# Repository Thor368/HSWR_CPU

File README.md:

# HSWR_CPU
This is the CPU board of the HochSchulWechselRichter V1 (HSWR1_CPU)

Differences to VESC:
- no FAULT pin
- no DC_cal pin
- EN_GATE inverted

This project is depricated and was replaced by the HSWR2:
https://github.com/Thor368/HSWR_V2

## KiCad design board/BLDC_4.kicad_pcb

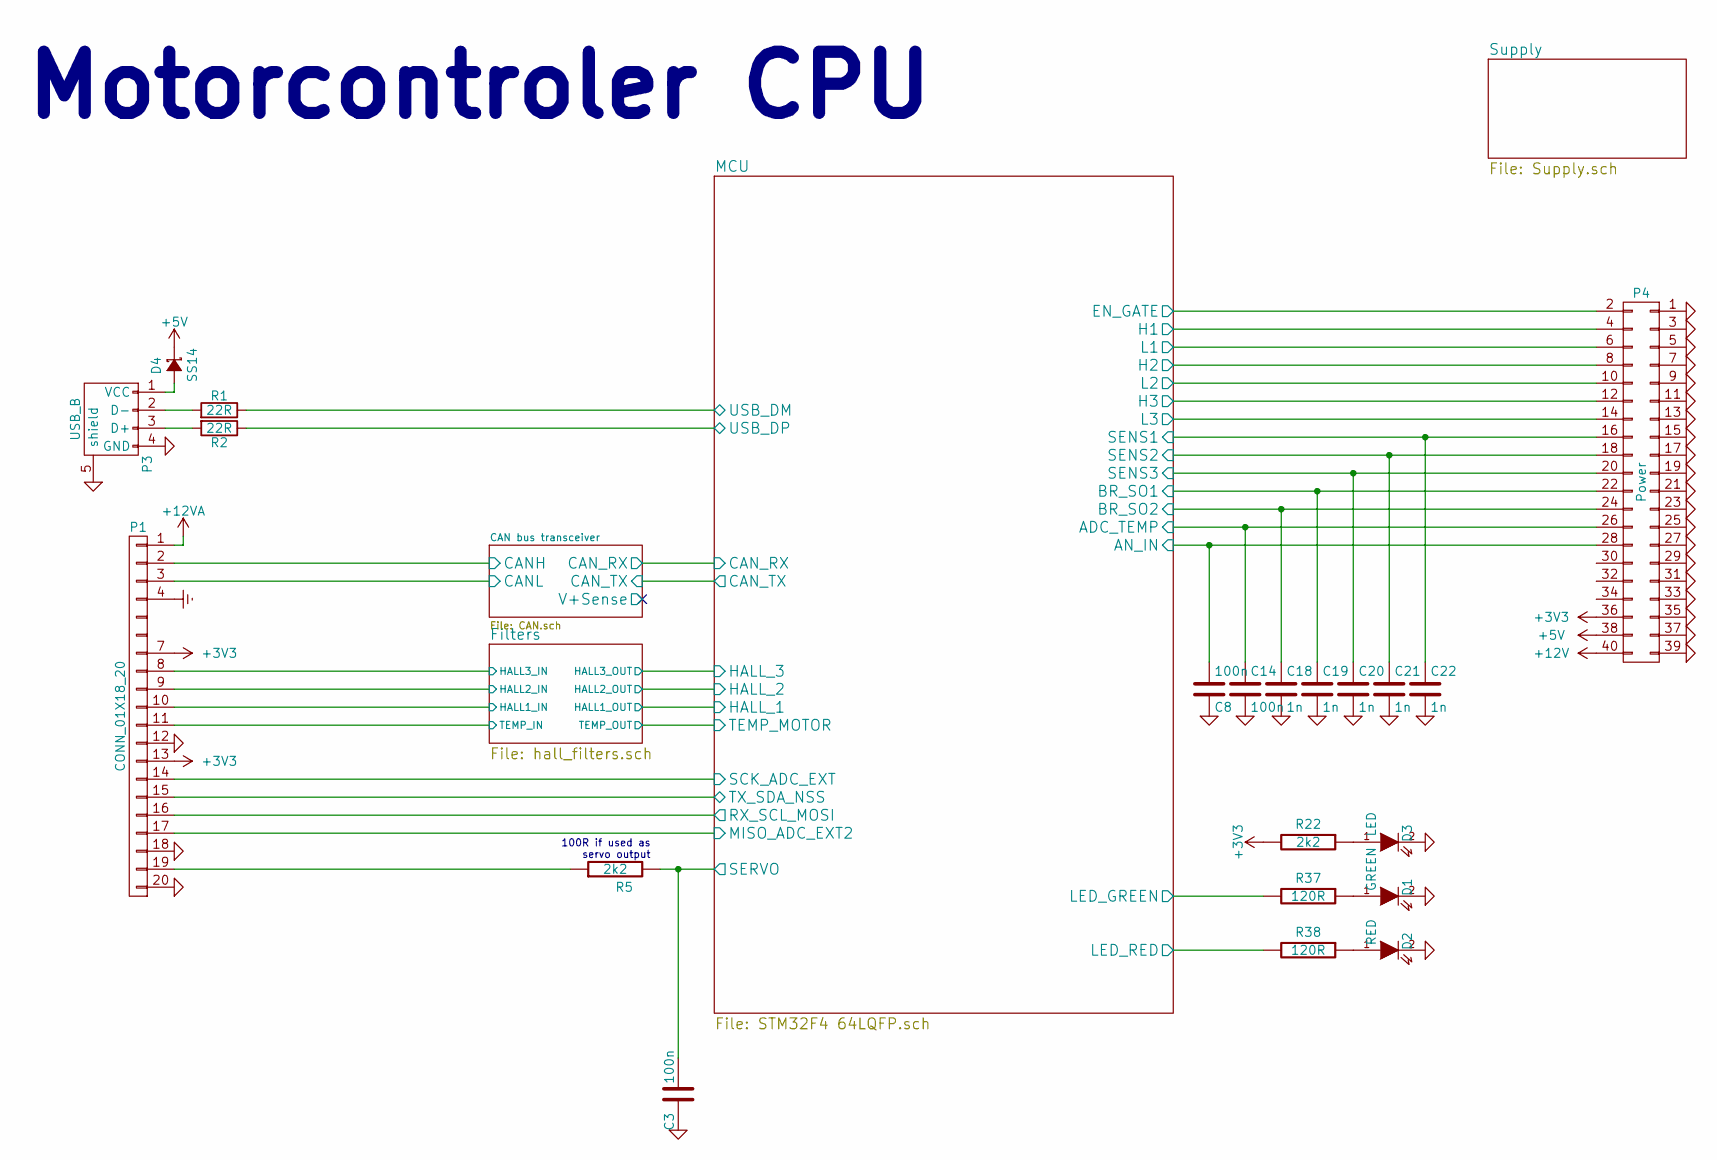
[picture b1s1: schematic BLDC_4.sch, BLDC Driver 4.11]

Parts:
C3, C8, C14: 100n; C_0805
C18, C19, C20, C21, C22: 1n; C_0805
D1: GREEN; LED_0805
D2: RED; LED_0805
D3: LED; LED_0805
D4: SS14; SMA_Standard
P1: CONN_01X18_20; XG4A_20_wo_56
P3: USB_B; USBB_vert
P4: Power; XG4A_40
R1, R2: 22R; R_0805
R5, R22: 2k2; R_0805
R37, R38: 120R; R_0805

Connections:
+3V3: P1.7, P1.13, P4.36, R22.2; also elsewhere on the board
+5V: D4.1 (K), P4.38; also elsewhere on the board
+12V: P4.40; also elsewhere on the board
+12VA: P1.1; also elsewhere on the board
/CAN bus transceiver/CANH: P1.2; also elsewhere on the board
/CAN bus transceiver/CANL: P1.3; also elsewhere on the board
/Filters/HALL1_IN: P1.10; also elsewhere on the board
/Filters/HALL2_IN: P1.9; also elsewhere on the board
/Filters/HALL3_IN: P1.8; also elsewhere on the board
/Filters/TEMP_IN: P1.11; also elsewhere on the board
/MCU/ADC_TEMP: C14.1, P4.26; also elsewhere on the board
/MCU/AN_IN: C8.2, P4.28; also elsewhere on the board
/MCU/BR_SO1: C19.1, P4.22; also elsewhere on the board
/MCU/BR_SO2: C18.1, P4.24; also elsewhere on the board
/MCU/EN_GATE: P4.2; also elsewhere on the board
/MCU/H1: P4.4; also elsewhere on the board
/MCU/H2: P4.8; also elsewhere on the board
/MCU/H3: P4.12; also elsewhere on the board
/MCU/L1: P4.6; also elsewhere on the board
/MCU/L2: P4.10; also elsewhere on the board
/MCU/L3: P4.14; also elsewhere on the board
/MCU/LED_GREEN: R37.2; also elsewhere on the board
/MCU/LED_RED: R38.2; also elsewhere on the board
/MCU/MISO_ADC_EXT2: P1.17; also elsewhere on the board
/MCU/RX_SCL_MOSI: P1.16; also elsewhere on the board
/MCU/SCK_ADC_EXT: P1.14; also elsewhere on the board
/MCU/SENS1: C22.1, P4.16; also elsewhere on the board
/MCU/SENS2: C21.1, P4.18; also elsewhere on the board
/MCU/SENS3: C20.1, P4.20; also elsewhere on the board
/MCU/SERVO: C3.2, R5.2; also elsewhere on the board
/MCU/TX_SDA_NSS: P1.15; also elsewhere on the board
/MCU/USB_DM: R1.1; also elsewhere on the board
/MCU/USB_DP: R2.1; also elsewhere on the board
Earth: P1.4; also elsewhere on the board
GND: C3.1, C8.1, C14.2, C18.2, C19.2, C20.2, C21.2, C22.2, D1.2 (K), D2.2 (K), D3.2 (K), P1.12, P1.18, P1.20, P3.4 (GND), P3.5 (shield), P4.1, P4.3, P4.5, P4.7, P4.9, P4.11, P4.13, P4.15, P4.17, P4.19, P4.21, P4.23, P4.25, P4.27, P4.29, P4.31, P4.33, P4.35, P4.37, P4.39; also elsewhere on the board
unnamed: D1.1 (A), R37.1
unnamed: D2.1 (A), R38.1
unnamed: D3.1 (A), R22.1
unnamed: D4.2 (A), P3.1 (VCC)
unnamed: P1.19, R5.1
unnamed: P3.2 (D-), R1.2
unnamed: P3.3 (D+), R2.2

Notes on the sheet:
100R if used as servo output
Motorcontroler CPU

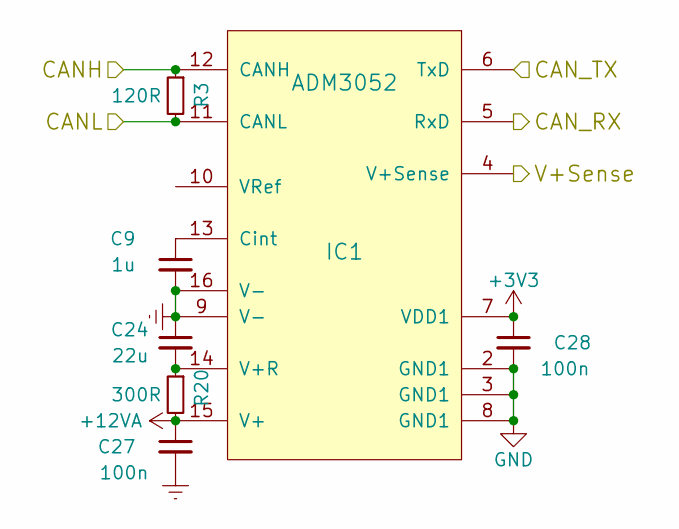
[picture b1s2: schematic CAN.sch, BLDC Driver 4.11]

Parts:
C9: 1u; C_0805
C24: 22u; C_0805
C27, C28: 100n; C_0805
IC1: ADM3052; SOIC-16_7.5x10.3mm_Pitch1.27mm
R3: 120R; R_0805
R20: 300R; R_1206

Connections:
+3V3: C28.1, IC1.7 (VDD1); also elsewhere on the board
+12VA: C27.1, IC1.15 (V+), R20.2; also elsewhere on the board
/CAN bus transceiver/CANH: IC1.12 (CANH), R3.1; also elsewhere on the board
/CAN bus transceiver/CANL: IC1.11 (CANL), R3.2; also elsewhere on the board
/CAN bus transceiver/CAN_RX: IC1.5 (RxD); also elsewhere on the board
/CAN bus transceiver/CAN_TX: IC1.6 (TxD); also elsewhere on the board
Earth: C9.2, C24.1, C27.2, IC1.9 (V-), IC1.16 (V-); also elsewhere on the board
GND: C28.2, IC1.2 (GND1), IC1.3 (GND1), IC1.8 (GND1); also elsewhere on the board
unnamed: C9.1, IC1.13 (Cint)
unnamed: C24.2, IC1.14 (V+R), R20.1

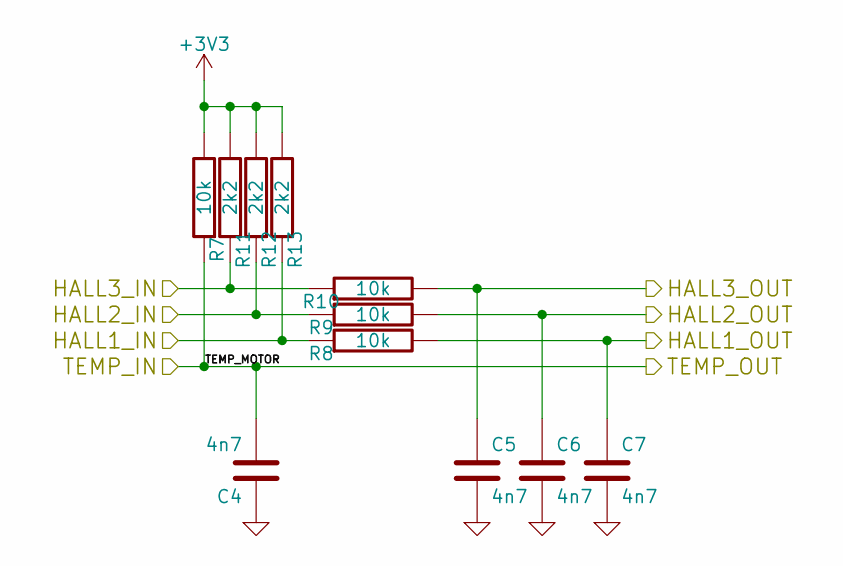
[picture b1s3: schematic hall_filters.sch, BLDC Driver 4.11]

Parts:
C4, C5, C6, C7: 4n7; C_0805
R7, R8, R9, R10: 10k; R_0805
R11, R12, R13: 2k2; R_0805

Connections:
+3V3: R7.2, R11.2, R12.2, R13.2; also elsewhere on the board
/Filters/HALL1_IN: R8.1, R13.1; also elsewhere on the board
/Filters/HALL1_OUT: C7.1, R8.2; also elsewhere on the board
/Filters/HALL2_IN: R9.1, R12.1; also elsewhere on the board
/Filters/HALL2_OUT: C6.1, R9.2; also elsewhere on the board
/Filters/HALL3_IN: R10.1, R11.1; also elsewhere on the board
/Filters/HALL3_OUT: C5.1, R10.2; also elsewhere on the board
/Filters/TEMP_IN: C4.2, R7.1; also elsewhere on the board
GND: C4.1, C5.2, C6.2, C7.2; also elsewhere on the board

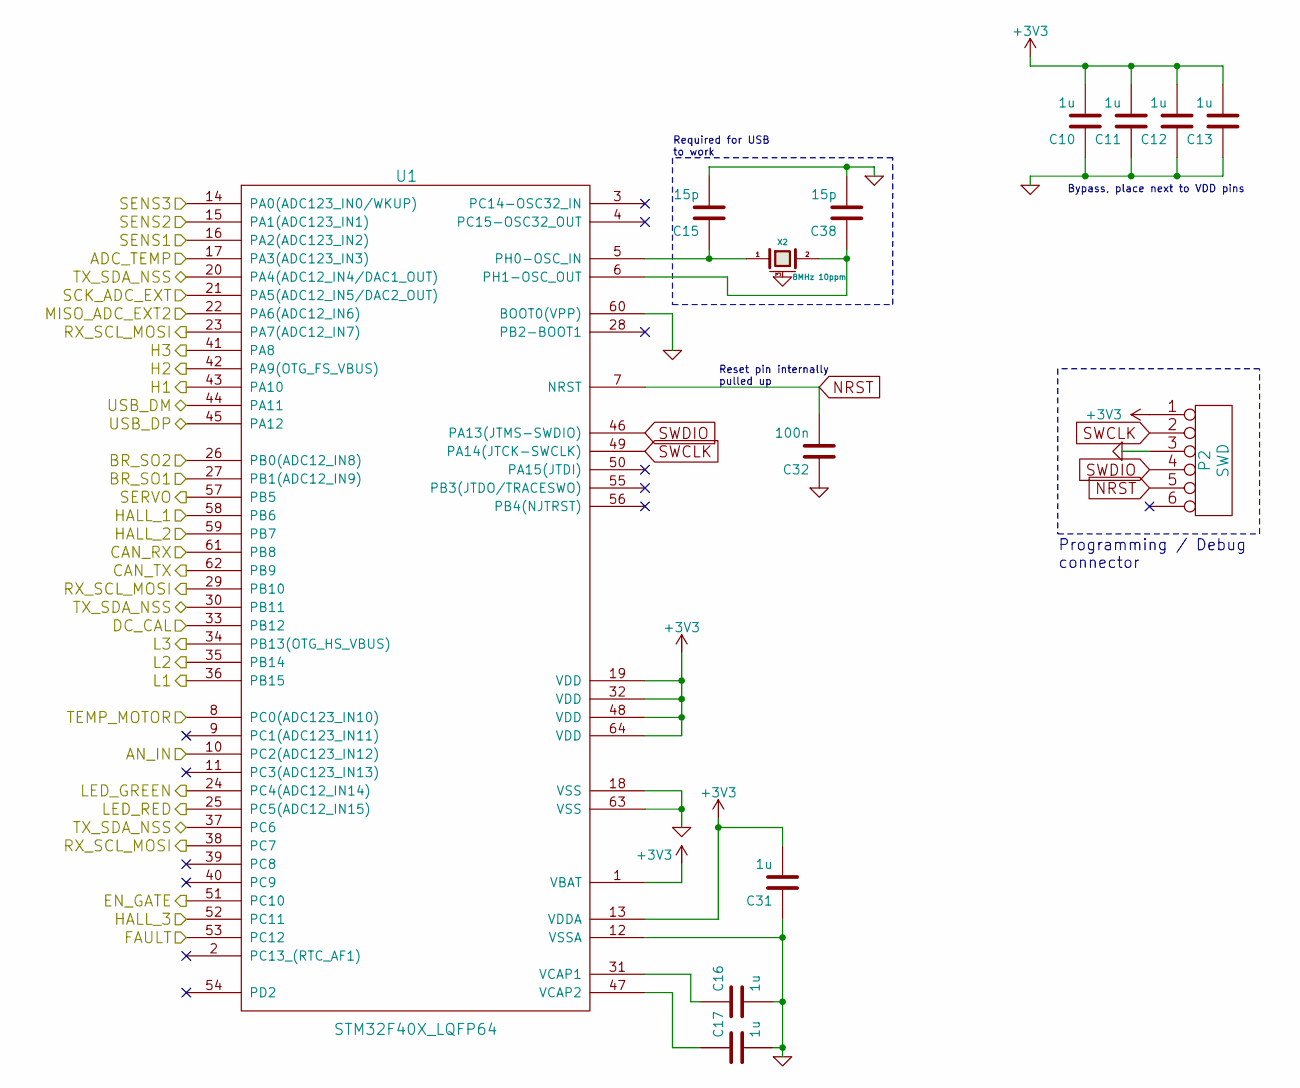
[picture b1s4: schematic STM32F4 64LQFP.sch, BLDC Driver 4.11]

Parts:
C10, C11, C12, C13, C16, C17, C31: 1u; C_0805
C15, C38: 15p; C_0805
C32: 100n; C_0805
P2: SWD; Pin_Header_Straight_2x03
U1: STM32F40X_LQFP64; LQFP-64_10x10mm_Pitch0.5mm
X2: 8MHz 10ppm; Crystal_HC49-U_Vertical; mfg# ABM3B-8.0-10-1UT

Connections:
+3V3: C10.2, C11.2, C12.2, C13.2, C31.2, P2.1, U1.1 (VBAT), U1.13 (VDDA), U1.19 (VDD), U1.32 (VDD), U1.48 (VDD), U1.64 (VDD); also elsewhere on the board
/CAN bus transceiver/CAN_RX: U1.61 (PB8); also elsewhere on the board
/CAN bus transceiver/CAN_TX: U1.62 (PB9); also elsewhere on the board
/Filters/HALL1_OUT: U1.58 (PB6); also elsewhere on the board
/Filters/HALL2_OUT: U1.59 (PB7); also elsewhere on the board
/Filters/HALL3_OUT: U1.52 (PC11); also elsewhere on the board
/Filters/TEMP_IN: U1.8 (PC0(ADC123_IN10)); also elsewhere on the board
/MCU/ADC_TEMP: U1.17 (PA3(ADC123_IN3)); also elsewhere on the board
/MCU/AN_IN: U1.10 (PC2(ADC123_IN12)); also elsewhere on the board
/MCU/BR_SO1: U1.27 (PB1(ADC12_IN9)); also elsewhere on the board
/MCU/BR_SO2: U1.26 (PB0(ADC12_IN8)); also elsewhere on the board
/MCU/EN_GATE: U1.51 (PC10); also elsewhere on the board
/MCU/H1: U1.43 (PA10); also elsewhere on the board
/MCU/H2: U1.42 (PA9(OTG_FS_VBUS)); also elsewhere on the board
/MCU/H3: U1.41 (PA8); also elsewhere on the board
/MCU/L1: U1.36 (PB15); also elsewhere on the board
/MCU/L2: U1.35 (PB14); also elsewhere on the board
/MCU/L3: U1.34 (PB13(OTG_HS_VBUS)); also elsewhere on the board
/MCU/LED_GREEN: U1.24 (PC4(ADC12_IN14)); also elsewhere on the board
/MCU/LED_RED: U1.25 (PC5(ADC12_IN15)); also elsewhere on the board
/MCU/MISO_ADC_EXT2: U1.22 (PA6(ADC12_IN6)); also elsewhere on the board
/MCU/RX_SCL_MOSI: U1.23 (PA7(ADC12_IN7)), U1.29 (PB10), U1.38 (PC7); also elsewhere on the board
/MCU/SCK_ADC_EXT: U1.21 (PA5(ADC12_IN5/DAC2_OUT)); also elsewhere on the board
/MCU/SENS1: U1.16 (PA2(ADC123_IN2)); also elsewhere on the board
/MCU/SENS2: U1.15 (PA1(ADC123_IN1)); also elsewhere on the board
/MCU/SENS3: U1.14 (PA0(ADC123_IN0/WKUP)); also elsewhere on the board
/MCU/SERVO: U1.57 (PB5); also elsewhere on the board
/MCU/TX_SDA_NSS: U1.20 (PA4(ADC12_IN4/DAC1_OUT)), U1.30 (PB11), U1.37 (PC6); also elsewhere on the board
/MCU/USB_DM: U1.44 (PA11); also elsewhere on the board
/MCU/USB_DP: U1.45 (PA12); also elsewhere on the board
GND: C10.1, C11.1, C12.1, C13.1, C15.2, C16.2, C17.2, C31.1, C32.1, C38.2, P2.3, U1.12 (VSSA), U1.18 (VSS), U1.60 (BOOT0(VPP)), U1.63 (VSS), X2.3 (case); also elsewhere on the board
NRST: C32.2, P2.5, U1.7 (NRST)
unnamed: C15.1, U1.5 (PH0-OSC_IN), X2.1
unnamed: C16.1, U1.31 (VCAP1)
unnamed: C17.1, U1.47 (VCAP2)
unnamed: C38.1, U1.6 (PH1-OSC_OUT), X2.2
SWCLK: P2.2, U1.49 (PA14(JTCK-SWCLK))
SWDIO: P2.4, U1.46 (PA13(JTMS-SWDIO))

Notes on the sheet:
Programming / Debug connector
Reset pin internally pulled up
Required for USB to work
Bypass, place next to VDD pins

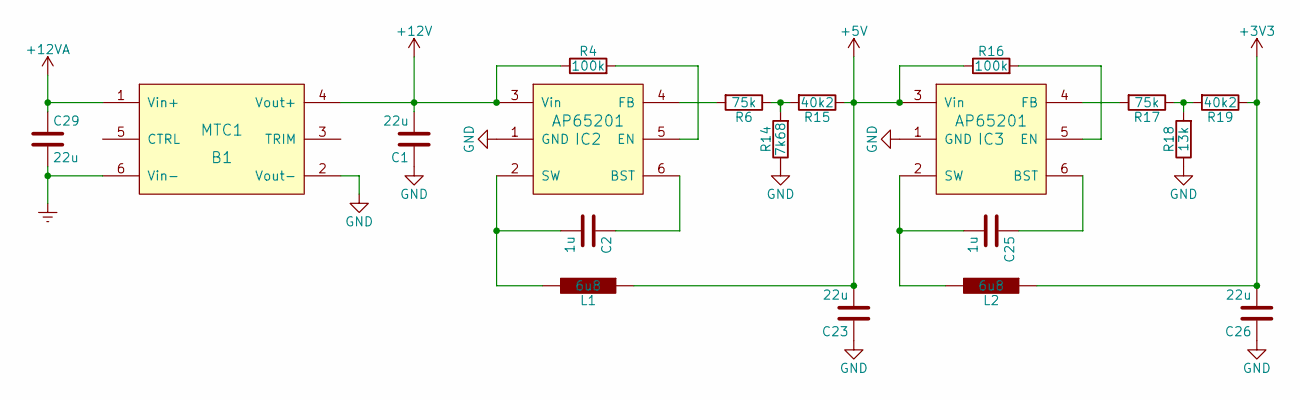
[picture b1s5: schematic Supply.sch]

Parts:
B1: MTC1
C1, C23, C26, C29: 22u; C_0805
C2, C25: 1u; C_0805
IC2, IC3: AP65201; SOT-23-6
L1, L2: 6u8; SRN4026
R4, R16: 100k; R_0805
R6, R17: 75k; R_0805
R14: 7k68; R_0805
R15, R19: 40k2; R_0805
R18: 13k; R_0805

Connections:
+3V3: C26.2, L2.1, R19.1; also elsewhere on the board
+5V: C23.2, IC3.3 (Vin), L1.1, R15.1, R16.1; also elsewhere on the board
+12V: B1.4 (Vout+), C1.2, IC2.3 (Vin), R4.1; also elsewhere on the board
+12VA: B1.1 (Vin+), C29.1; also elsewhere on the board
Earth: B1.6 (Vin-), C29.2; also elsewhere on the board
GND: B1.2 (Vout-), C1.1, C23.1, C26.1, IC2.1 (GND), IC3.1 (GND), R14.1, R18.1; also elsewhere on the board
unnamed: C2.1, IC2.6 (BST)
unnamed: C2.2, IC2.2 (SW), L1.2
unnamed: C25.1, IC3.6 (BST)
unnamed: C25.2, IC3.2 (SW), L2.2
unnamed: IC2.4 (FB), R6.2
unnamed: IC2.5 (EN), R4.2
unnamed: IC3.4 (FB), R17.2
unnamed: IC3.5 (EN), R16.2
unnamed: R6.1, R14.2, R15.2
unnamed: R17.1, R18.2, R19.2

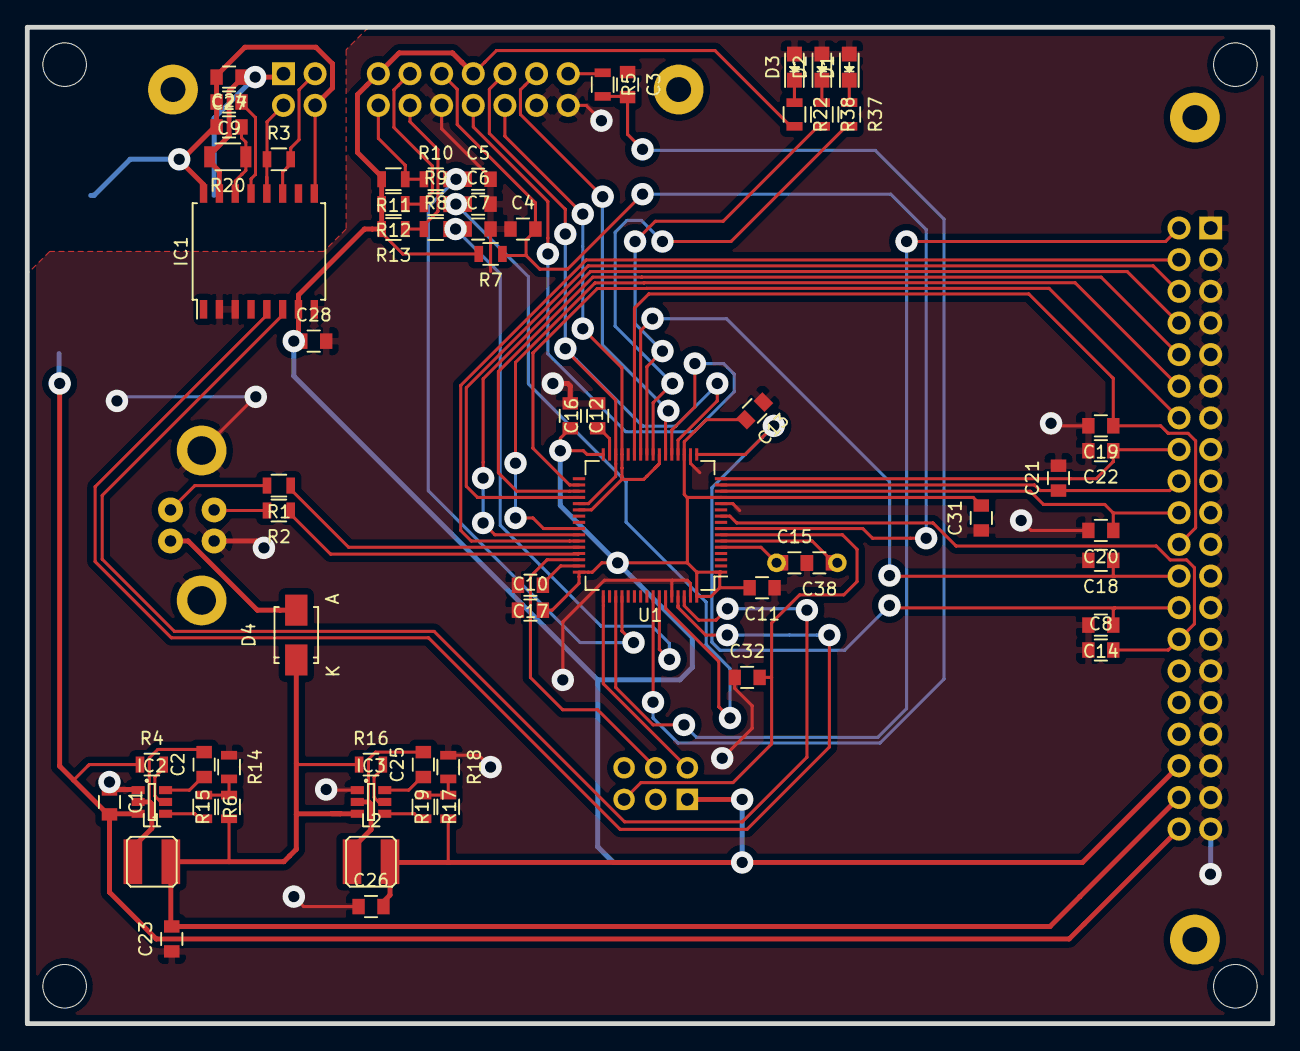
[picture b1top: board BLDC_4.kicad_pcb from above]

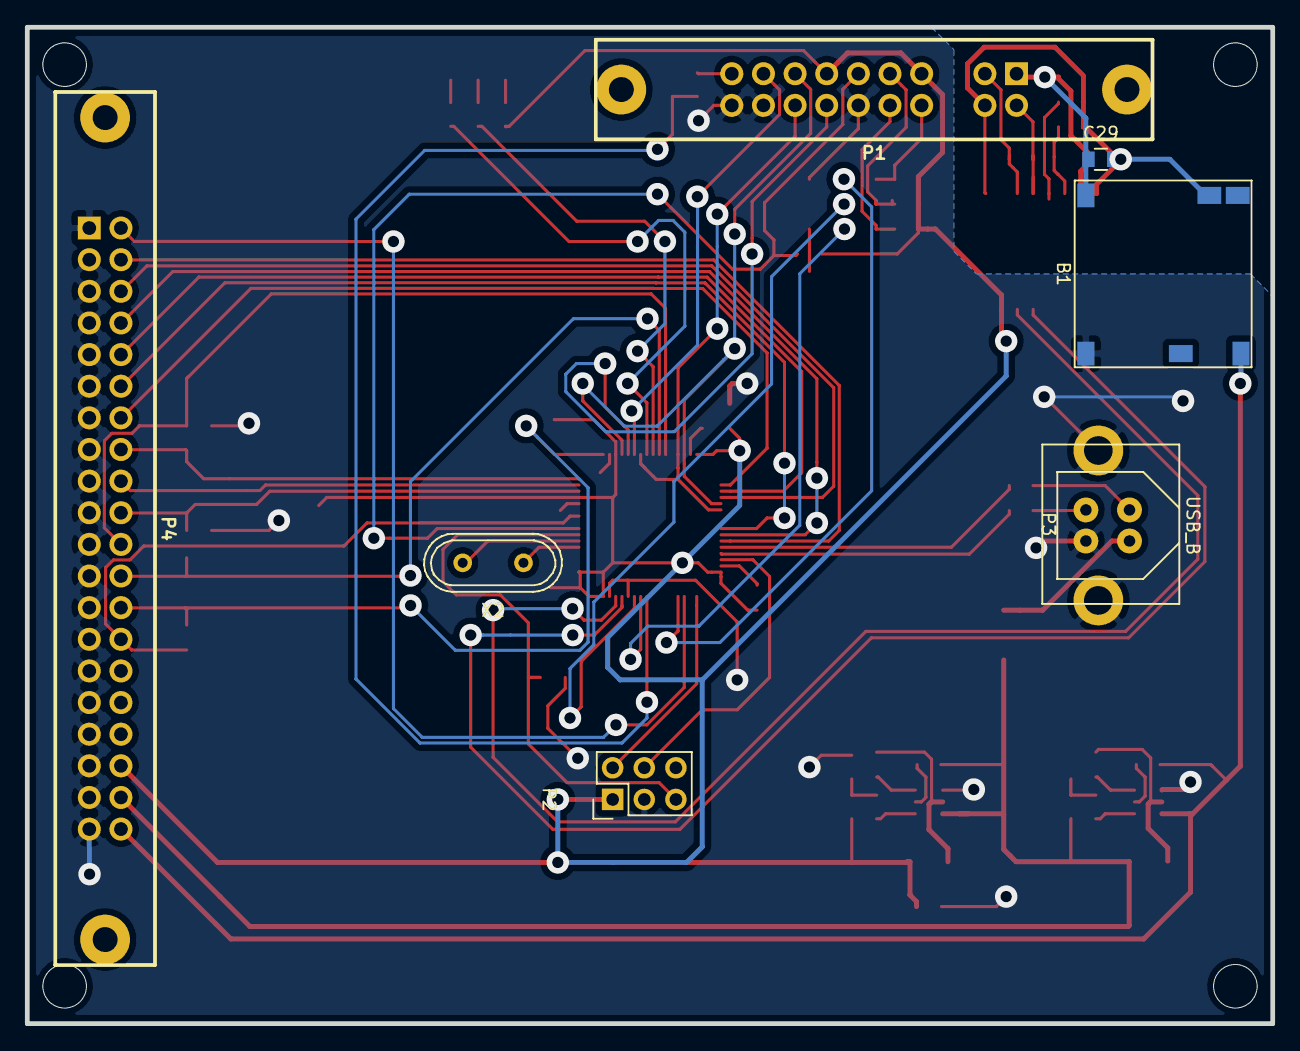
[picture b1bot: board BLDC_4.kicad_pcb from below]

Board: 2 copper layers, 100.0 x 80.0 mm, 71 parts (7 on the bottom side), 66 nets.

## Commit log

2016-06-03 - commit of first iteration
2016-06-03 first few words
2016-06-03 readme: added difs to VESC
2016-06-03 - changed some more Vcc labels to +3V3 - combined all input connectors into one big connector - changed can transceiver to MAX3051 - removed HV pin from power connector -> divider now on PS board - u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
2016-06-07 - preliminary layout for CPU board ready
2016-06-07 - some power supply changes
2016-06-09 - updated layout with recent changes in schematic
2016-06-10 - CAN interface isolation
2016-06-23 - small optimisations - fixed connector on wrong layer
2016-06-23 - added mounting holes - added outline
2017-11-29 Update README.md
    - added deprication note and link to HSWR2
